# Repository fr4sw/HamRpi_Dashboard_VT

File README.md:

Projet de l'Association Réunionaise des Radio Amateurs

Objectif Global : permettre la supervision de l'autonomie des stations automatiques basées sur RaspberryPi

La carte permet :
de remonter au RaspberryPi diverses informations :
- Présence du 5V (GPIO 16) avec isolation galvanique par optocoupleur
- Tension d'alimentation 12V (via ADC) par pont diviseur (à ajuster)
- Tension d'alimentation 3,3V issu du RaspberryPi (via ADC)
- Température par CTN externes (2 canaux) (ajuster les résistances) (via ADC)

les tensions (et températures) sont remontées par un ADS1115 sur le bus I2C (Ad 0x48 par défaut, modifiable par JP1)

de commander le RaspberryPi :
- 3 boutons (GPIO 20, 21, 12)

D'afficher des états :
- une LED (GPIO06)

Le PCB a été lancé en fabrication (JLCPCB) le 2 juillet, fourni à l'ARRA le 15/7/26 -> release 1.0

Date : 15 juillet 2026

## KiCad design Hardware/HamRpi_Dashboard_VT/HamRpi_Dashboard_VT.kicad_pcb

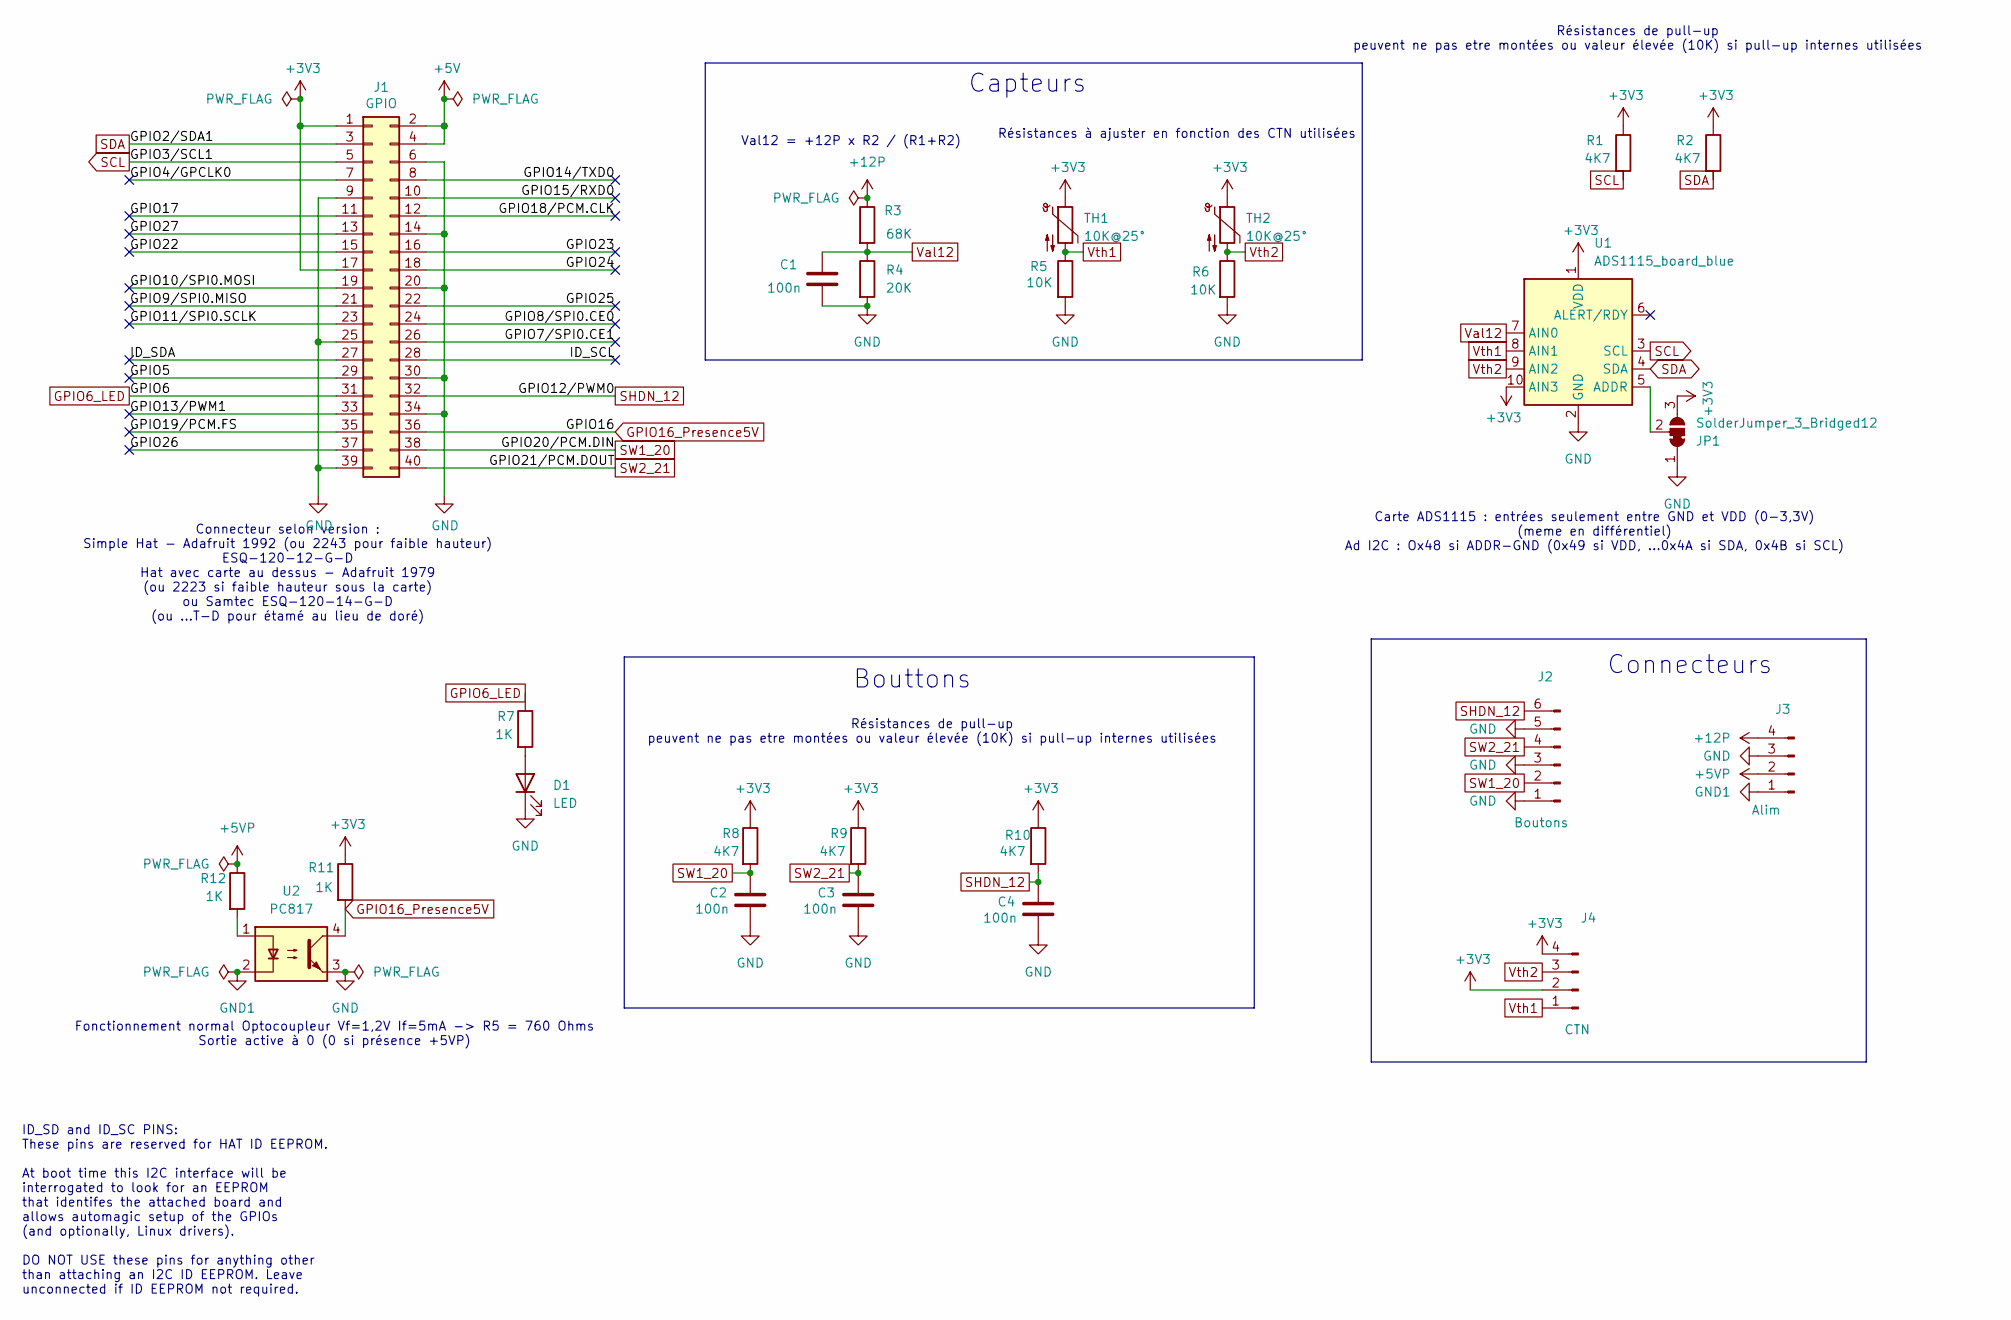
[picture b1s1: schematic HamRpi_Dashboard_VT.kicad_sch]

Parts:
C1, C2, C3, C4: 100n; C_Disc_D4.7mm_W2.5mm_P5.00mm; MPN FG28X7R1H104KNT06
D1: LED; LED_D5.0mm
J1: GPIO; PinSocket_2x20_P2.54mm_Vertical; MPN 1979
J2: Boutons; PinHeader_1x06_P2.54mm_Vertical_NetName
J3: Alim; PinHeader_1x04_P2.54mm_Vertical_NetName
J4: CTN; PinHeader_1x04_P2.54mm_Vertical_NetName
JP1: SolderJumper_3_Bridged12; SolderJumper-3_P1.3mm_Bridged12_RoundedPad1.0x1.5mm_NumberL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
R1, R2, R8, R9, R10: 4K7; R_Axial_DIN0207_L6.3mm_D2.5mm_P7.62mm_Horizontal; MPN MFR-25FRF52-4K7
R3: 68K; R_Axial_DIN0207_L6.3mm_D2.5mm_P7.62mm_Horizontal; MPN MFR-25FRF52-68K
R4: 20K; R_Axial_DIN0207_L6.3mm_D2.5mm_P7.62mm_Horizontal; MPN MFR-25FRF52-20K
R5, R6: 10K; R_Axial_DIN0207_L6.3mm_D2.5mm_P7.62mm_Horizontal; MPN MFR-25FRF52-10K
R7, R11, R12: 1K; R_Axial_DIN0207_L6.3mm_D2.5mm_P7.62mm_Horizontal; MPN MFR-25FRF52-1K
TH1, TH2: 10K@25°; R_Axial_DIN0204_L3.6mm_D1.6mm_P5.08mm_Horizontal; MPN NTCLE100E3103HT1
U1: ADS1115_board_blue; Adafruit_ADS1115_modifie; MPN 26203
U2: PC817; DIP-4_W7.62mm; MPN PC817X1NSZ0F

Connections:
+3V3: J1.1, J1.17, J4.2, J4.4, JP1.3 (B), R1.1, R2.1, R8.1, R9.1, R10.1, R11.1, TH1.1, TH2.1, U1.1 (VDD), U1.10 (AIN3)
+5V: J1.2, J1.4
+5VP: J3.2, R12.1
+12P: J3.4, R3.1
/GPIO4/GPCLK0: J1.7
/GPIO5: J1.29
/GPIO7/SPI0.CE1: J1.26
/GPIO8/SPI0.CE0: J1.24
/GPIO9/SPI0.MISO: J1.21
/GPIO10/SPI0.MOSI: J1.19
/GPIO11/SPI0.SCLK: J1.23
/GPIO13/PWM1: J1.33
/GPIO14/TXD0: J1.8
/GPIO15/RXD0: J1.10
/GPIO17: J1.11
/GPIO18/PCM.CLK: J1.12
/GPIO19/PCM.FS: J1.35
/GPIO22: J1.15
/GPIO23: J1.16
/GPIO24: J1.18
/GPIO25: J1.22
/GPIO26: J1.37
/GPIO27: J1.13
/ID_SCL: J1.28
/ID_SDA: J1.27
GND: C1.2, C2.2, C3.2, C4.2, D1.1 (K), J1.6, J1.9, J1.14, J1.20, J1.25, J1.30, J1.34, J1.39, J2.1, J2.3, J2.5, J3.3, JP1.1 (A), R4.2, R5.2, R6.2, U1.2 (GND), U2.3
GND1: J3.1, U2.2
GPIO6_LED: J1.31, R7.1
GPIO16_Presence5V: J1.36, R11.2, U2.4
unnamed: D1.2 (A), R7.2
unnamed: JP1.2 (C), U1.5 (ADDR)
unnamed: R12.2, U2.1
SCL: J1.5, R1.2, U1.3 (SCL)
SDA: J1.3, R2.2, U1.4 (SDA)
SHDN_12: C4.1, J1.32, J2.6, R10.2
SW1_20: C2.1, J1.38, J2.2, R8.2
SW2_21: C3.1, J1.40, J2.4, R9.2
Val12: C1.1, R3.2, R4.1, U1.7 (AIN0)
Vth1: J4.1, R5.1, TH1.2, U1.8 (AIN1)
Vth2: J4.3, R6.1, TH2.2, U1.9 (AIN2)

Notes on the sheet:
Résistances de pull-up peuvent ne pas etre montées ou valeur élevée (10K) si pull-up internes utilisées
Val12 = +12P x R2 / (R1+R2)
Connecteurs
Capteurs
Résistances à ajuster en fonction des CTN utilisées
Connecteur selon version : Simple Hat - Adafruit 1992 (ou 2243 pour faible hauteur) ESQ-120-12-G-D Hat avec carte au dessus - Adafruit 1979 (ou 2223 si faible hauteur sous la carte) ou Samtec ESQ-120-14-G-D (ou ...T-D pour étamé au lieu de doré)
ID_SD and ID_SC PINS: These pins are reserved for HAT ID EEPROM. At boot time this I2C interface will be interrogated to look for an EEPROM that identifes the attached board and allows automagic setup of the GPIOs (and optionally, Linux drivers). DO NOT USE these pins for anything other than attach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
Carte ADS1115 : entrées seulement entre GND et VDD (0-3,3V) (meme en différentiel) Ad I2C : Ox48 si ADDR-GND (0x49 si VDD, ...0x4A si SDA, 0x4B si SCL)
Bouttons
Fonctionnement normal Optocoupleur Vf=1,2V If=5mA -> R5 = 760 Ohms Sortie active à 0 (0 si présence +5VP)

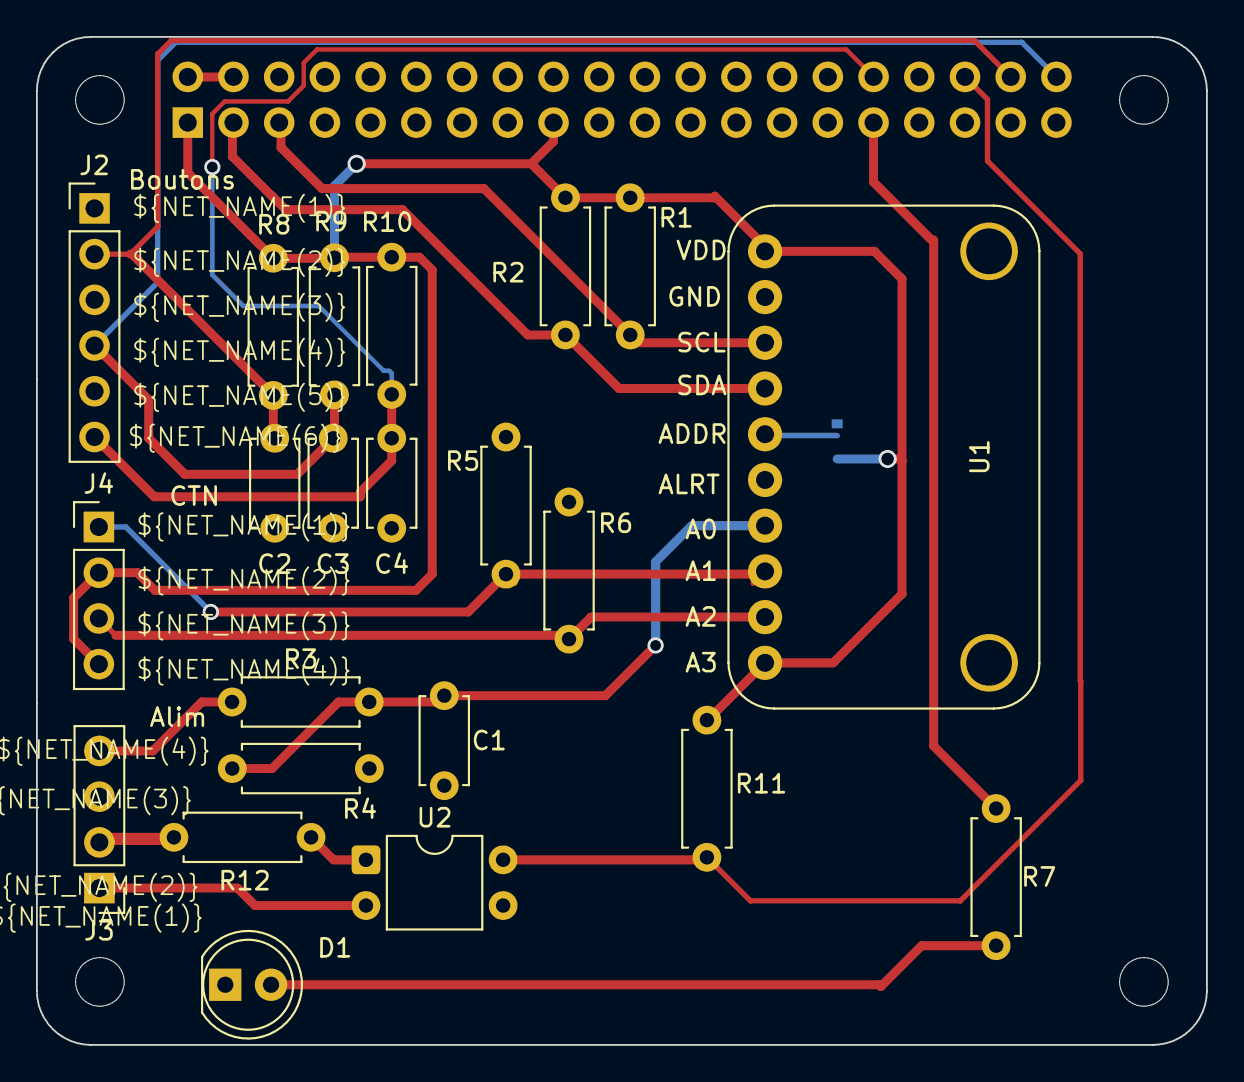
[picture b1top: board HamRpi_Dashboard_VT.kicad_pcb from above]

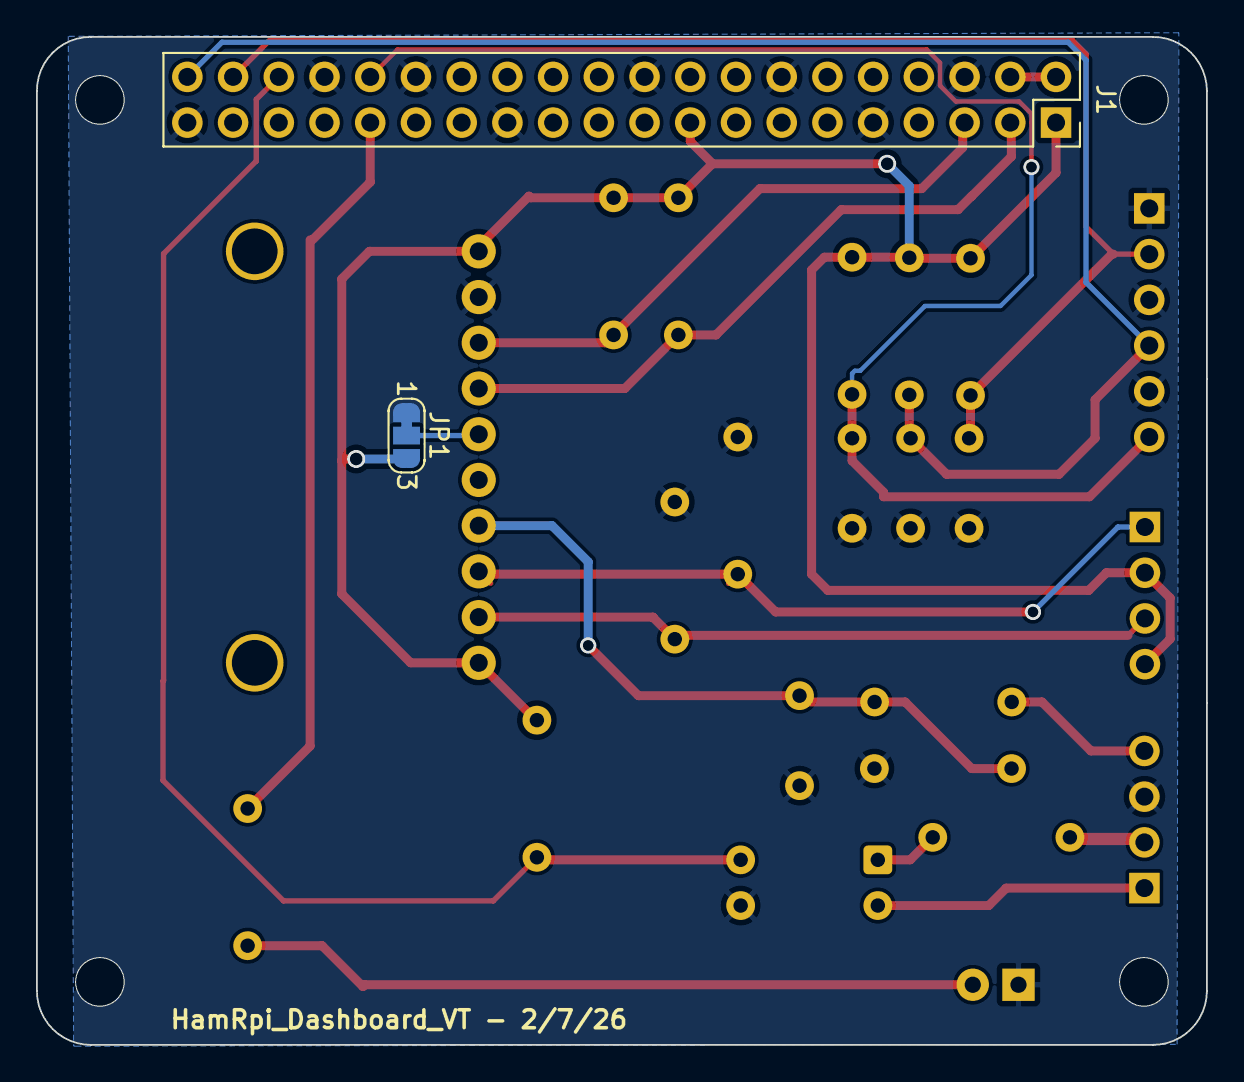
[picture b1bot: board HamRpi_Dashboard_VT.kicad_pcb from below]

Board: 2 copper layers, 65.0 x 56.0 mm, 28 parts (2 on the bottom side), 19 nets.

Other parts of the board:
MH1, MH2, MH3, MH4: MountingHole_2.7mm_M2.5
